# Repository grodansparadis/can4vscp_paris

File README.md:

-----

<h1>Paris Relay module</h1>

This module is part of the VSCP project. It is free to use, modify and sell. The only thing we kindly ask is that improvements and extensions are contributed back to the project (at your will). This to make the project better for everyone. All design files is licensed under the MIT license.

In the repository you find the development files for the Kelvin NTC10K module. The project is also the base reference for a VSCP implementation on a Microchip 18F PIC device together with the [Kelvin NTC10K module](https://github.com/grodansparadis/can4vscp-kelvin-ntc10k)

## Abstract

Paris is a relay module that connects to a CAN4VSCP bus and can control up to seven external relays. The module can be attached to a standard DIN Rail or be mounted directly on a wall.

The module fully adopts to the CAN4VSCP specification and can be powered directly over the bus with a 9-28V DC power source. It has a rich register set for configuration and any information events defined. It also have a decision matrix for easy dynamic event handling.

VSCP CAN modules are designed to work on a VSCP4CAN bus which use ordinary RJ-45 connectors and is powered with 9-28V DC over the same cable. This means there is no need for a separate power cable. All that is needed is a CAT5 or better twisted pair cable. Buss length can be a maximum of 500 meters with drops of maximum 24 meters length (up to a total of 120 meters). As for all VSCP4CAN modules the communication speed is fixed at 125 kbps.

All VSCP modules contains information of there own setup, manual, hardware version, manufacturer etc. You just ask the module for the information you need and you will get it. When they are started up they have a default functionality that often is all that is needed to get a working setup. If the module have something to report it will send you an event and if it is setup to react on a certain type of event it will do it's work when you send event(s) to it. 

<hr>

## Project files

### User manual
  * [User Manual](https://grodansparadis.github.io/can4vscp-paris/#)

### Schematic, PCB, 3D files etc
  * [Schematics reversion B](./eagle/paris_revb_sch.png)
 * Hardware design files is made in [KiCad](https://kicad.org) and can be found in the `kicad` directory. Valid from reversion B of the hardware.
   * Gerber files for PCB production can be found in the `gerber` directory (in the `kicad` folder).
 * Eagle schema and board files for reversion A and B can be found in the `eagle` directory. Only the KiCad version is actively updated.

 ### Firmware

 The firmware is developed in [MPLAB X IDE](https://www.microchip.com/mplab/mplab-x-ide) using the [XC8 compiler](https://www.microchip.com/mplab/compilers).

  * Binary release files is available [here](https://github.com/grodansparadis/can4vscp-paris/releases)

### MDF - Module Description File(s)
  * [MDF file version: 1.1.3 Release date: 2022-03-25](http://www.eurosource.se/paris_010.xml)
  * [MDF file version: 0.0.2 Release date: 2009-10-07](http://www.eurosource.se/paris_001.xml)

### Support
If you need support, please open an issue in the [GitHub repository](https://github.com/grodansparadis/can4vscp-paris/issues).

### Buy a ready made modules
You can buy a ready made module from [Grodans Paradis](http://www.grodansparadis.com).

### Project related links
  * [VSCP project](https://www.vscp.org)
  * [VSCP Documentation site](https://docs.vscp.org/)
  * [VSCP Wiki](https://github.com/grodansparadis/vscp/wiki)

## Steps you should go through to adopt this file for your own VSCP project.

  * The frequency for your system may be different. This will affect the CAN bit rate settings which are defined in the biginning of the can18f.c file. Here you also find the filter/mask  defines if you need to change these. Timer0 is used as a 1 ms timer for the VSCP functionality. You should adopt the timer reload value in the main.h file to your system.

  * The GUID (Glocal Unique ID) is defined in the beginning of vscp.c This number should be different for each piece of equiment you produce. Regard it is as the device serial number. It can be moved to EEPROM if that is found more convinient. In that case the vscp_rcv_readreg  procedure in vscp.c also has to be changed.

  * The device URL is defined in the beginning of the vscp.c file. This is an URL without the initial "http://" that should point to a XML file that give information about your piece of equipment.

  * The manufacturer id is also defined in the beginning of the vscp.c file. You can use this id in any way you like.

In addition to this you may use different pins for the INIT button (RC0 today) and the status LED (RC1) today. Changes affect the main interrupt vector.

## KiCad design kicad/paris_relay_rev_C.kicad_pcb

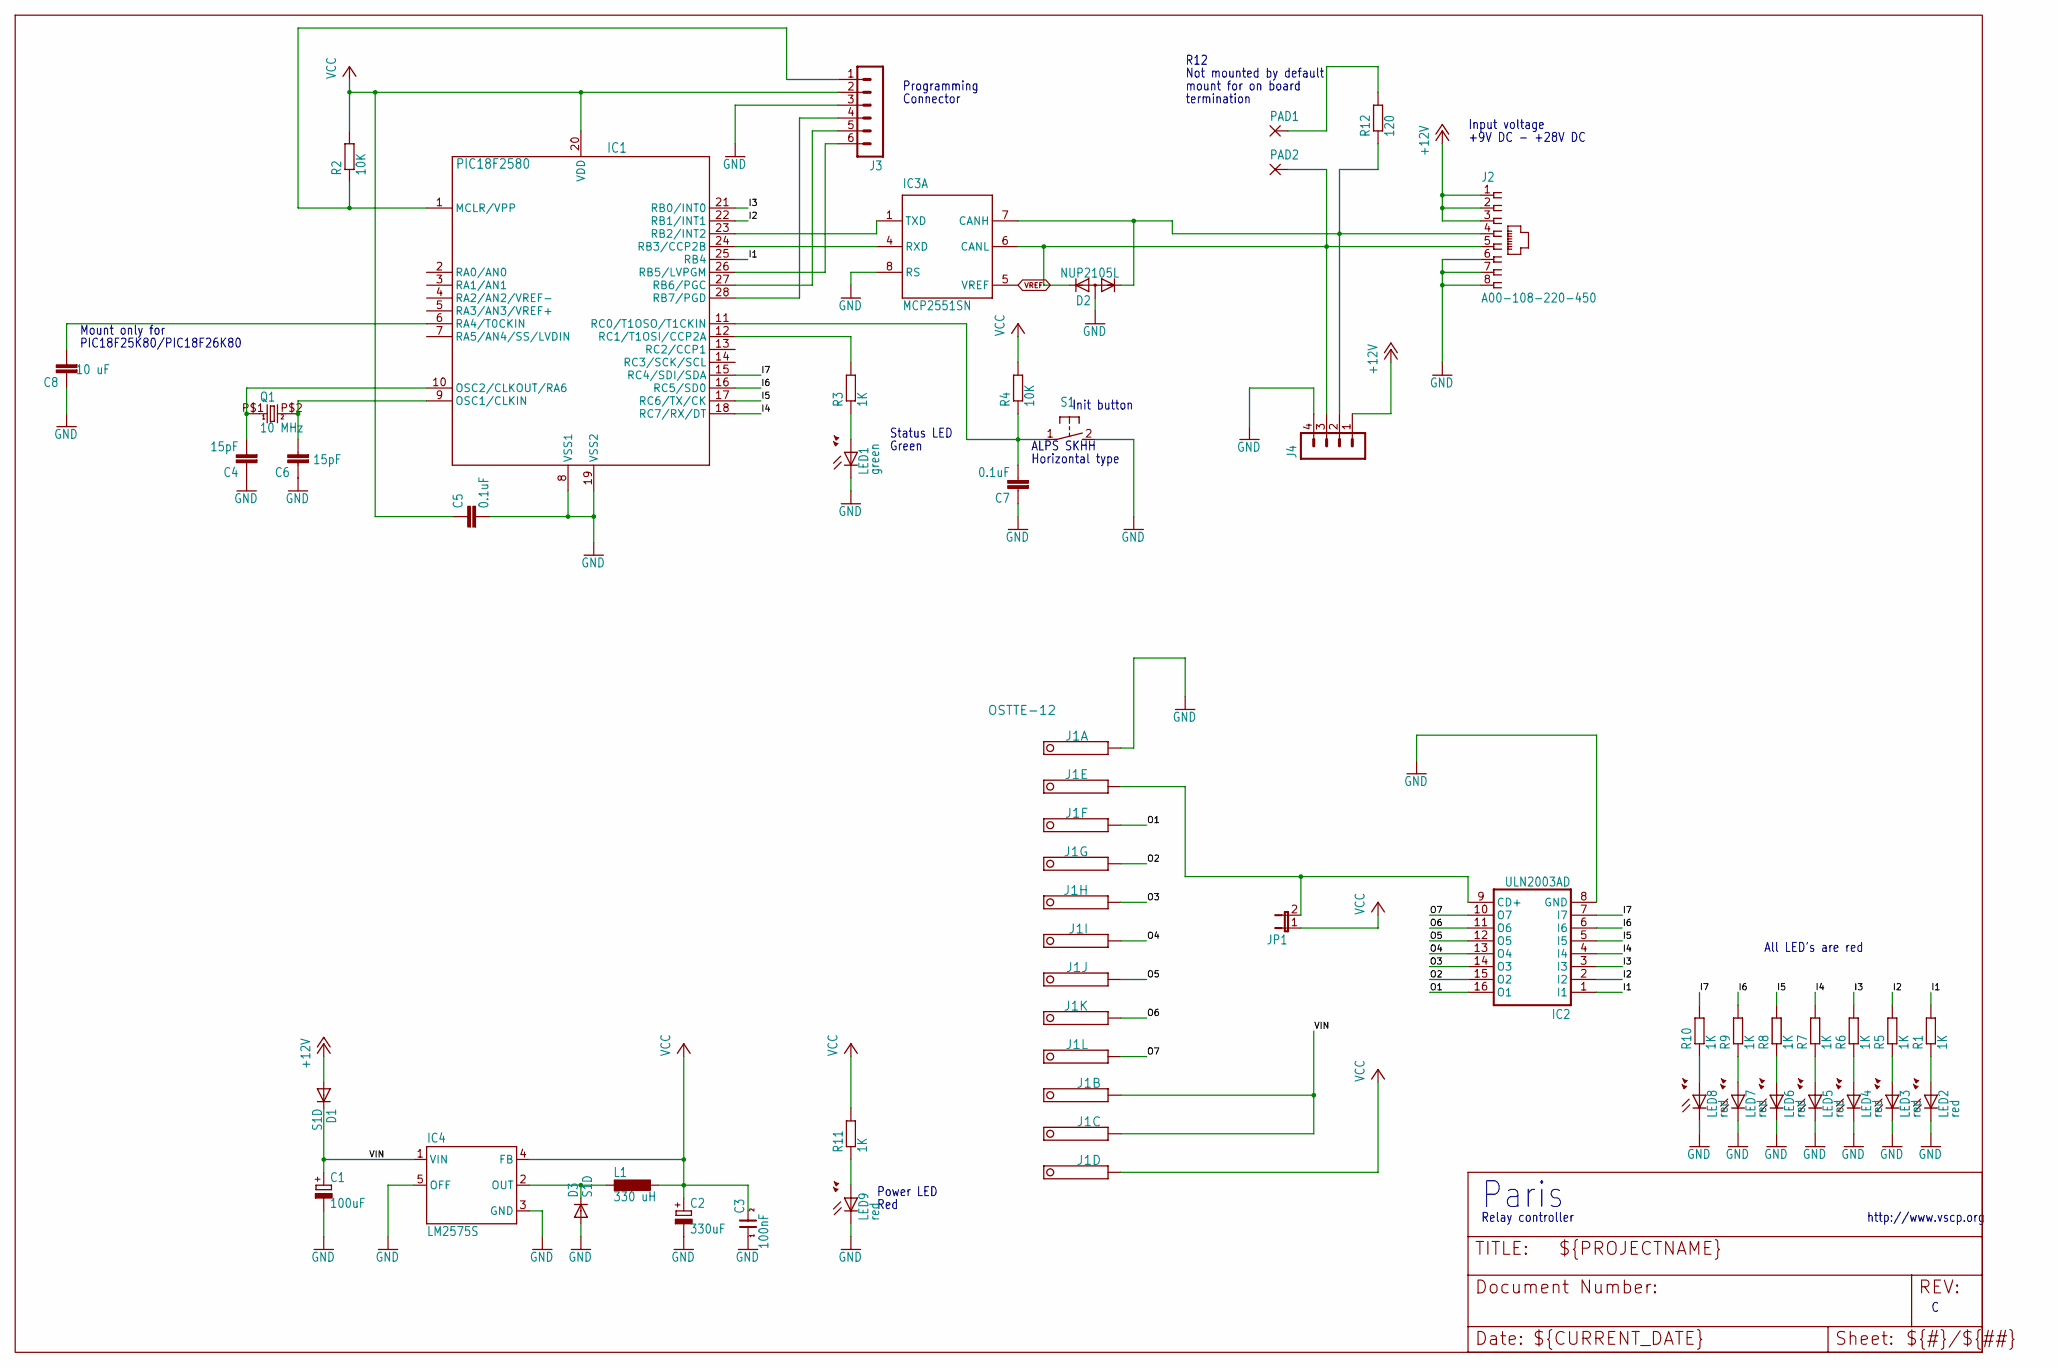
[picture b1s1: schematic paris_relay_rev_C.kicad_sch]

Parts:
C1: 100uF; PANASONIC_D
C2: 330uF; PANASONIC_D
C3: 100nF; 0805
C4, C6: 15pF; C0805
C5, C7: 0.1uF; C0805
C8: 10 uF; C0805
D1, D3: S1D; SOD123
D2: NUP2105L; SOT23
IC1: PIC18F2580; SO28
IC2: ULN2003AD; SO16
IC3: MCP2551SN; SO-08
IC4: LM2575S; TO263-5
J1: OSTTE-12; PINHEAD-12
J2: A00-108-220-450; RJ-45
J3: MA06-1
J4: MA04-1
JP1: JP1E; JP1
L1: 330 uH; DO3316P
LED1: green; CHIP-LED0805
LED2, LED3, LED4, LED5, LED6, LED7, LED8, LED9: red; CHIP-LED0805
PAD1, PAD2: 1,6/0,8; 1,6_0,8
Q1: 10 MHz; 9C
R1, R3, R5, R6, R7, R8, R9, R10, R11: 1K; R0805
R2, R4: 10K; R0805
R12: 120; R0805
S1: 31-XX; B3F-31XX

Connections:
+12V: D1.A, J2.1, J2.2, J2.3, J4.1
CANH: D2.1 (K1), IC3.7 (CANH), J2.4, J4.2, R12.1
CANL: D2.2 (K2), IC3.6 (CANL), J2.5, J4.3, PAD2.1
GND: C1.-, C2.-, C3.1, C4.1, C5.2, C6.1, C7.1, C8.1, D2.3 (A), D3.A, IC1.8 (VSS1), IC1.19 (VSS2), IC2.8 (GND), IC3.2 (VSS), IC3.8 (RS), IC4.3 (GND), IC4.5 (OFF), J1.1, J2.6, J2.7, J2.8, J3.3, J4.4, LED1.C, LED2.C, LED3.C, LED4.C, LED5.C, LED6.C, LED7.C, LED8.C, LED9.C, S1.2 (S)
I1: IC1.25 (RB4), IC2.1 (I1), R1.2
I2: IC1.22 (RB1/INT1), IC2.2 (I2), R5.2
I3: IC1.21 (RB0/INT0), IC2.3 (I3), R6.2
I4: IC1.18 (RC7/RX/DT), IC2.4 (I4), R7.2
I5: IC1.17 (RC6/TX/CK), IC2.5 (I5), R8.2
I6: IC1.16 (RC5/SD0), IC2.6 (I6), R9.2
I7: IC1.15 (RC4/SDI/SDA), IC2.7 (I7), R10.2
unnamed: D3.C, IC4.2 (OUT), L1.1
unnamed: C4.2, IC1.10 (OSC2/CLKOUT/RA6), Q1.P$1 (1)
unnamed: PAD1.1, R12.2
unnamed: IC1.12 (RC1/T1OSI/CCP2A), R3.2
unnamed: LED1.A, R3.1
unnamed: C7.2, IC1.11 (RC0/T1OSO/T1CKIN), R4.1, S1.1
unnamed: C6.2, IC1.9 (OSC1/CLKIN), Q1.P$2 (2)
unnamed: IC2.9 (CD+), J1.2, JP1.2
unnamed: LED2.A, R1.1
unnamed: LED3.A, R5.1
unnamed: LED4.A, R6.1
unnamed: IC1.1 (MCLR/VPP), J3.1, R2.1
unnamed: IC1.28 (RB7/PGD), J3.4
unnamed: IC1.27 (RB6/PGC), J3.5
unnamed: IC1.26 (RB5/LVPGM), J3.6
unnamed: LED5.A, R7.1
unnamed: LED6.A, R8.1
unnamed: LED7.A, R9.1
unnamed: LED8.A, R10.1
unnamed: LED9.A, R11.1
unnamed: C8.2, IC1.6 (RA4/T0CKIN)
O1: IC2.16 (O1), J1.3
O2: IC2.15 (O2), J1.4
O3: IC2.14 (O3), J1.5
O4: IC2.13 (O4), J1.6
O5: IC2.12 (O5), J1.7
O6: IC2.11 (O6), J1.8
O7: IC2.10 (O7), J1.9
RXCAN: IC1.24 (RB3/CCP2B), IC3.4 (RXD)
TXCAN: IC1.23 (RB2/INT2), IC3.1 (TXD)
VCC: C2.+, C3.2, C5.1, IC1.20 (VDD), IC3.3 (VDD), IC4.4 (FB), J1.12, J3.2, JP1.1, L1.2, R2.2, R4.2, R11.2
VIN: C1.+, D1.C, IC4.1 (VIN), J1.10, J1.11
VREF: IC3.5 (VREF)

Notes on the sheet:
mount for on board
R12
Programming
Red
Green
+9V DC - +28V DC
Init button
Status LED
ALPS SKHH
http://www.vscp.org
Power LED
Connector
Mount only for
PIC18F25K80/PIC18F26K80
Paris
All LED's are red
termination
Relay controller
Input voltage
Not mounted by default
Horizontal type

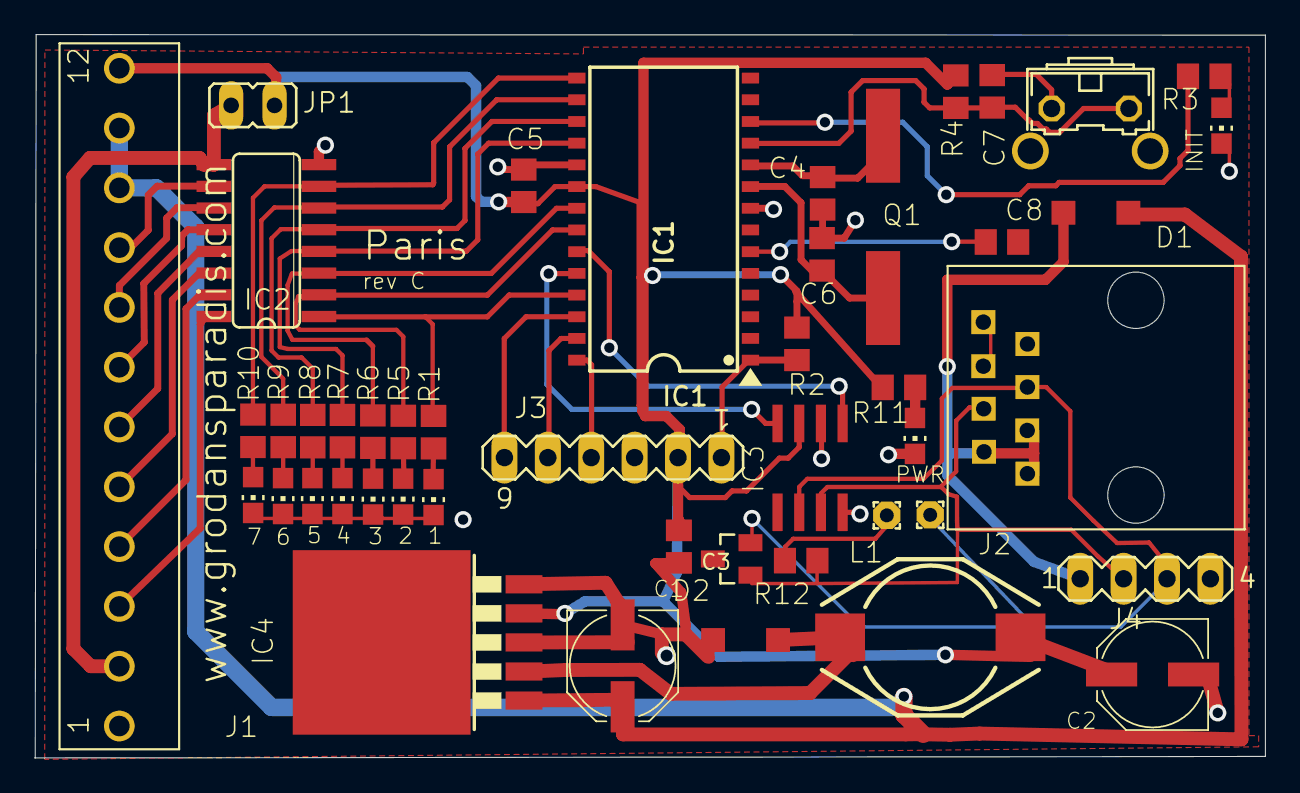
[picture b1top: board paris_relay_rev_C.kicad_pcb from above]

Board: 6 copper layers, 72.0 x 42.3 mm, 46 parts (0 on the bottom side), 43 nets.

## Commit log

2015-02-12 Move Paris from private repository to public
2015-02-12 Added project folder
2015-02-13 First checkin
2015-02-14 Rename
2015-02-14 Removed unused folder
2015-02-18 MDF folder moved
2015-03-03 Added missing update of vscp_configtimer
2015-03-04 Removed some junk from the doDm method
2015-03-24 Release 1.1.0
2015-03-24 Distro files
2015-04-02 Missing subzone check in dodm added.
2015-06-17 Fixed compile error
2015-06-24 Fixed pulse turn off when changing status
2015-06-24 Using peripheral eeprom functions now
2015-06-24 Edit
2015-07-27 Fixed problem with send timeout
2015-08-17 Added eagle files
2015-08-17 removed old bom
2015-08-17 Fixing some spelling errors
2015-08-17 Changed license to MIT
2015-08-21 added workfiles to ignore list
2015-08-21 Renamed signal name to CANH for clarity
2015-08-21 Added service/repair log
2015-08-23 Schema added
2015-08-23 Added old schema
2015-09-12 Removed some junk
2015-09-12 Removed some junk. Added some docs
2015-09-13 Zone and subzone check now is dune on relay level as they should. Changed channel_flags to register_flags
2015-09-13 Fixed invalid character problem in MDF
2015-09-13 Release 1.1.1
2015-09-14 Colorized mdf
2015-09-24 Formatted mdf
2015-11-11 Removed Kelvin NTC10K manual that was wrongly put in this folder
2015-11-11 Added missing manual
2015-11-13 Prepare for release 1.1.2
2015-11-13 Added firmware readme
2016-03-07 Added registersets for test
2016-03-08 Added some docs
2016-03-08 2016-03-08 AKHE - Adopted to 1.6 firmware. Adopted for PIC18F26K80
2016-03-08 Fixed copyright info.
2016-03-23 Fixed bug in control byte write routine
2016-03-23 Version 1.1.3
2016-03-23 Removed unused folders
2016-03-23 Removed intermediate hex
2016-03-23 Version 1.1.4
2016-03-23 Version 1.1.5
2016-04-11 2016-04-11 AKHE - vscp_getMatrixInfo nw use the pointer supplied by the framework.
2016-04-19 RA4 set to input to prevent collision with VCAP circuits in PIC18F2580. Brown out raised to maximum (3V & 4.6V). Valuable input from Anders Forsgren, AJE Electronics AB.
2016-04-19 work
2016-05-04 Added new link to bit timing
2016-10-19 Added stock pictures
2020-05-15 init timer is now 2500 ms instea dof 250 ms
2020-05-15 Updated firmware
2022-03-25 Fixed description of bits for action parameters
2025-02-07 Added raw docs from wiki
2025-02-07 Added vanilla docsify files
2025-02-07 Initial manual
2025-02-09 Moved docs from dokiwiki to markdown (docsify)
2025-02-09 Set correct version
2025-02-17 Updated README with OSH logo
2025-02-17 Updated reference module info
2025-02-17 Mention Pic 18F now
2025-08-18 Converted schema to kicad
2025-08-20 Adopted to latest VSCP firmware
2025-09-09 Added shorthand info about files
2025-09-09 Fixed path to latest MDF
2025-09-09 Fixed path for OHSW image
2025-09-09 Added history marker
2025-09-09 Fixed invalid references
2025-09-09 Updated manual date/version
2025-09-23 Added design-files folder
2025-09-30 Fixed link to issues
2025-09-30 Fixed some missing links due to repositoruy name change
2025-09-30 Formatted
2026-05-05 Updated license to CERN
